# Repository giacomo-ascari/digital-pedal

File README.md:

# DIGITAL PEDAL - G33KY-TOAD
This project aims at the creation of a multi-effect stompbox.
```
        ┌─┐_┌───┐    ┌─────┐    ┌───────┐    ┌─────┐       /│   \
┌┴┴┐════┴═════  │    │ ADC │    │  MCU  │    │ DAC │    ┌─┤ │  \ \
└┬┬┘════┬═════  │ -> │     │ -> │ [DSP] │ -> │     │ -> └─┤ │  / /
        └─┘‾└───┘    └─────┘    └───────┘    └─────┘       \│   /
                     └─────────────────────────────┘
                                G33KY-TOAD
                             [DIGITAL-PEDAL]
```

## Hardware
The system will have a STM32F407VGT6 at it's core, with its 168Mhz clock and 192kB of memory.
ADC? Still don't know.
DAC? Probably one already on the STM32F4 MCU.

## Pedals
|           Name          |     Family     |             DSP             | Amplitude | Time/ frequency | Implemented |
|:-----------------------:|:--------------:|:---------------------------:|:---------:|:---------------:|:-----------:|
| Amplifier               | Utilities      | Gain > hard clip            |     X     |                 |      X      |
| Bypass                  | Utilities      | Bypass signal (default)     |           |                 |      X      |
| Bitcrusher (resolution) | Distortion     | Reduce sample resolution    |     X     |                 |      X      |
| Dynamic amplifier       | Utilities      | Gain > hard clip            |     X     |        X        |     WIP     |
| Fuzz                    | Distortion     | Gain > hard clip > sum wave |     X     |                 |      X      |
| Low pass filter         | Filter         | Low pass filter             |           |        X        |      X      |
| Overdrive               | Distortion     | Gain > soft clip            |     X     |                 |      X      |
| Overdrive (log)         | Distortion     | Gain > soft clip            |     X     |                 |      X      |
| Tremolo                 | Distortion     | Multiply by wave            |     X     |                 |      X      |

## Would-be-nice-to-have pedals
|           Name          |     Family     |             DSP             | Amplitude | Time/ frequency |
|:-----------------------:|:--------------:|:---------------------------:|:---------:|:---------------:|
| Bitcrusher (rate)       | Distortion     | Reduce sampling rate        |           |        X        |
| Wah wah                 | Filter         |                             |           |        X        |
| Compressor              | Compression    |                             |     X     |        X        |
| Equalizer               | Equalisation   |                             |     X     |        X        |
| Delay/echo              | Delay Lines    |                             |           |        X        |
| Vibrato                 | Distortion     |                             |           |        X        |
| Flanger                 | Flangers       |                             |           |                 |
| Phaser                  | Phasers        |                             |           |        X        |
| Octaver                 | Pitch Shifting |                             |           |        X        |
| Chorus                  | Chorus         |                             |           |        X        |

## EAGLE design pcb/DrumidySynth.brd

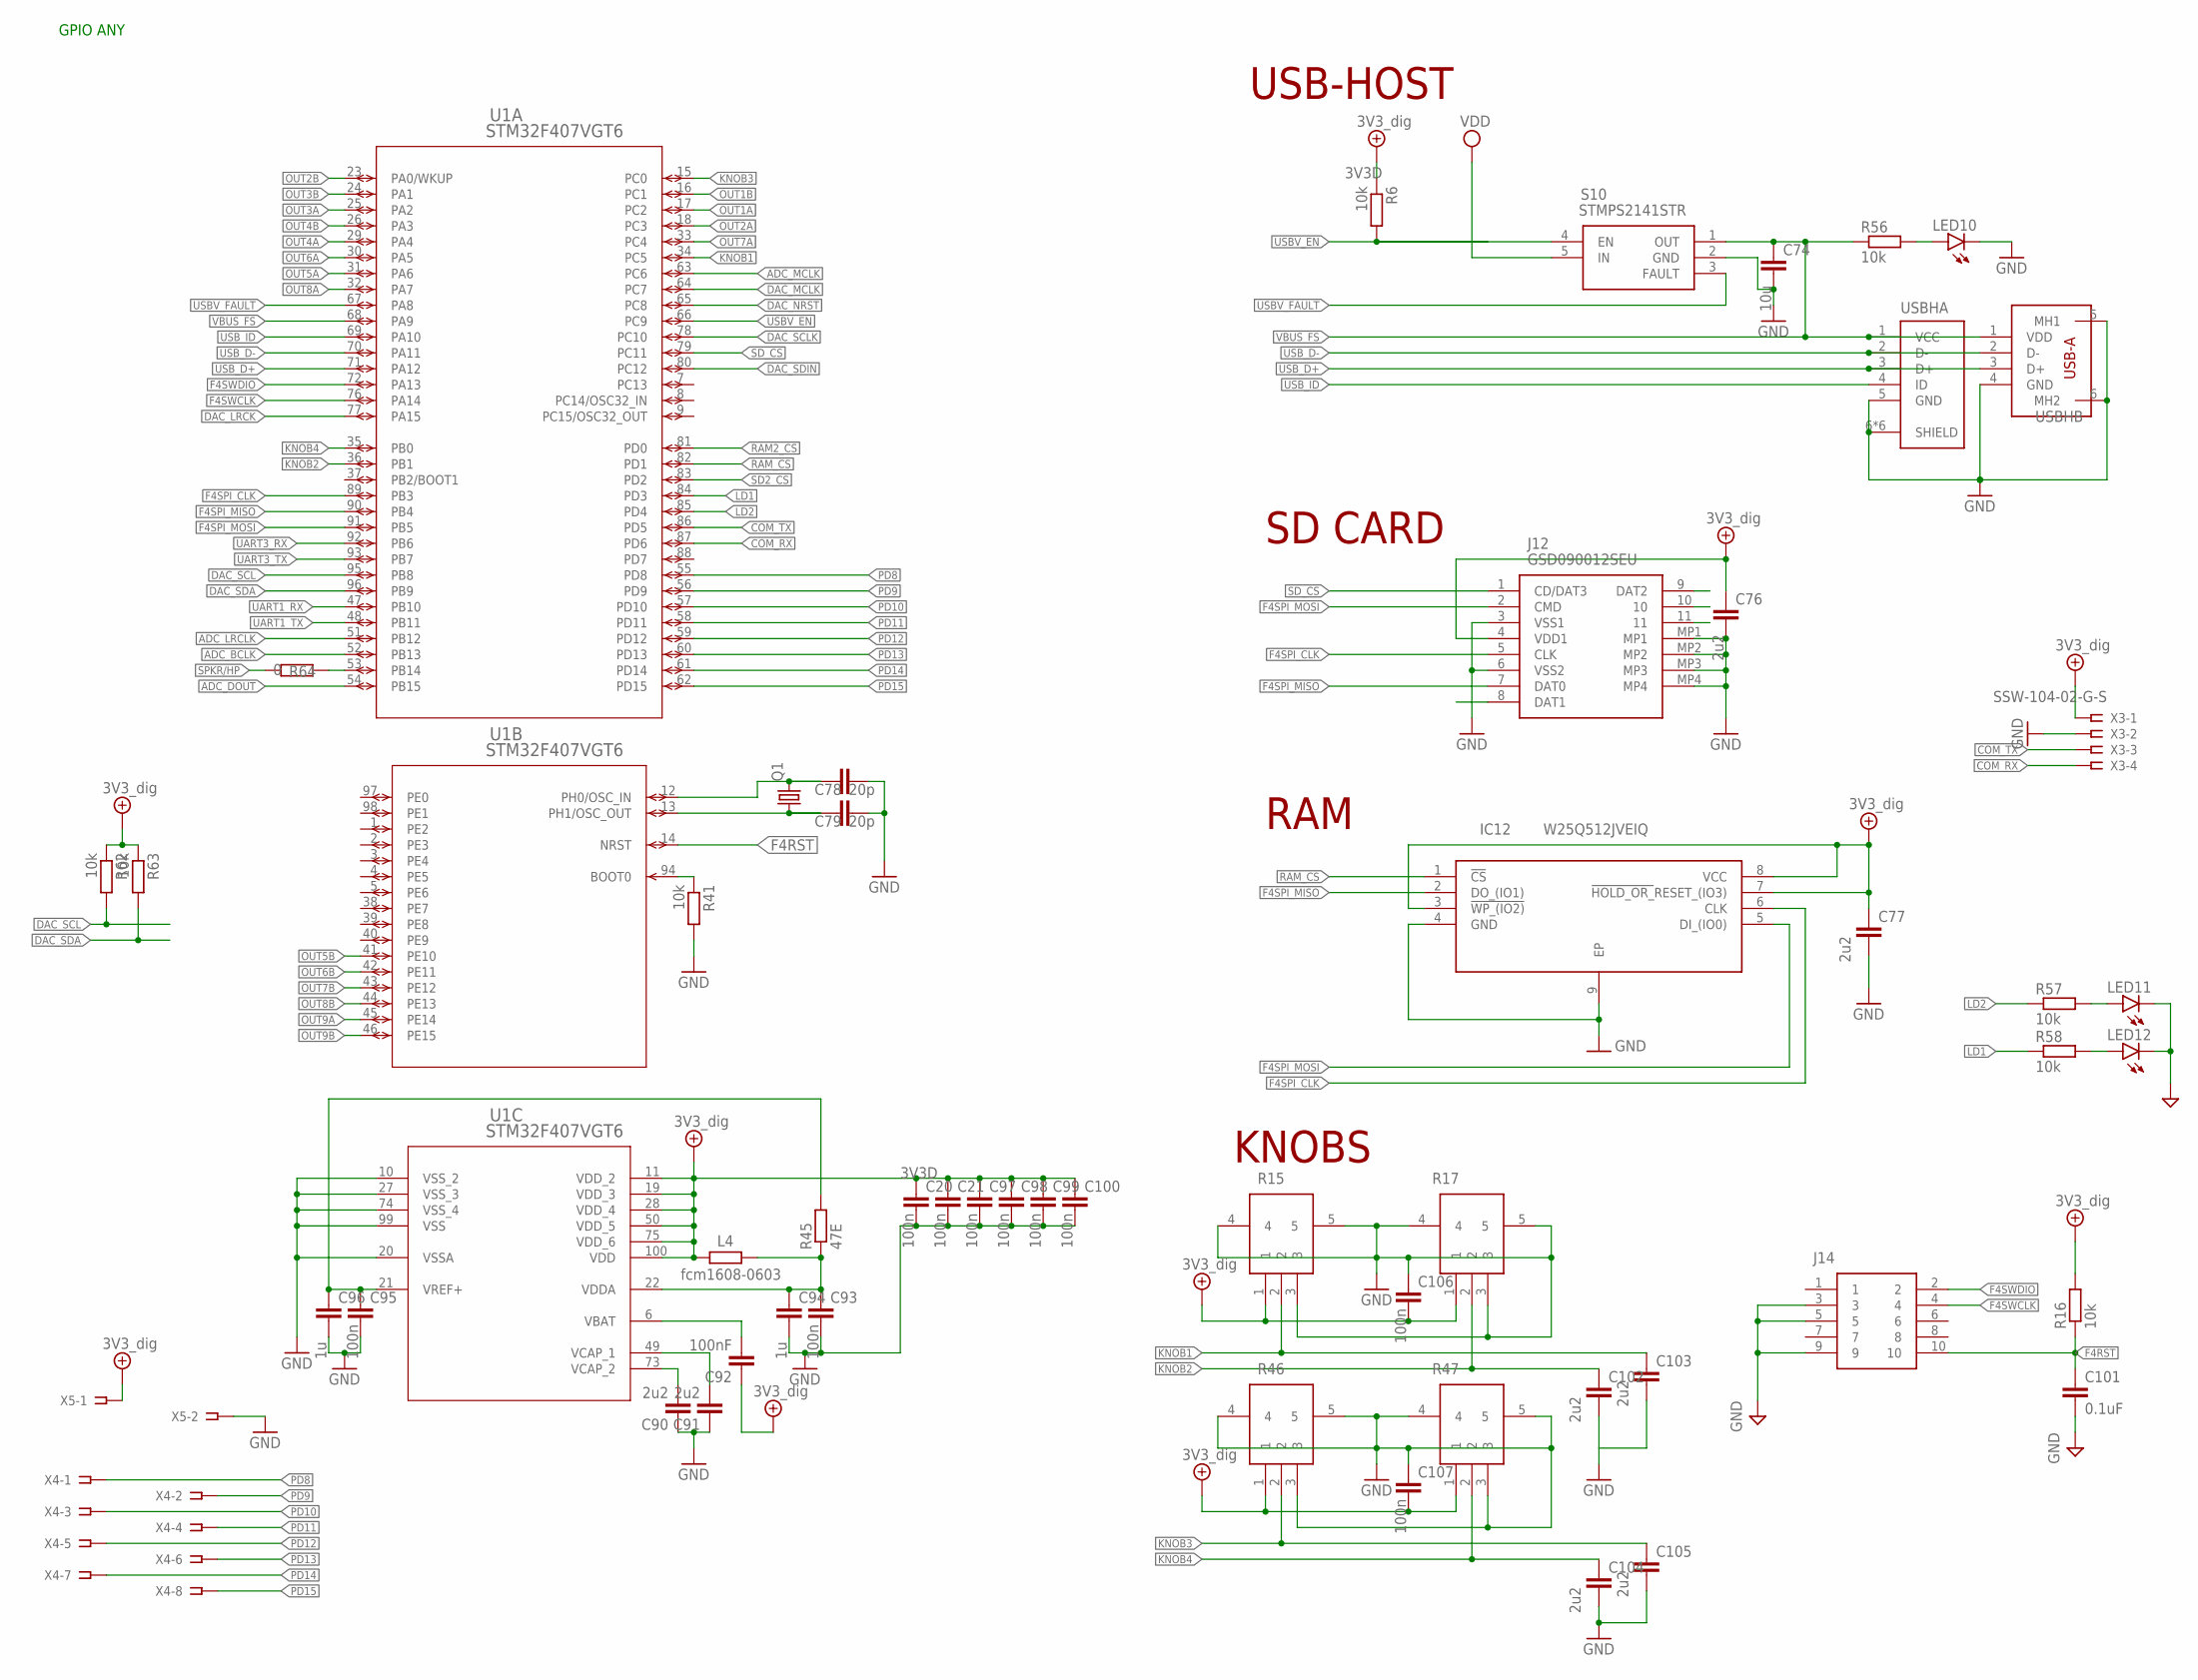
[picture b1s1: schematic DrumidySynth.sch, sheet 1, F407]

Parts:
C20, C21, C93, C95, C97, C98, C99, C100, C106, C107: 100n; C0603K
C74: 10u; C0805K
C76, C77, C102, C103, C104, C105: 2u2; C0805K
C78, C79: 20p; C0402K
C90, C91: 2u2; C0603K
C92: 100nF; C0603K
C94, C96: 1u; C0805K
C101: 0.1uF; C0402
IC12: W25Q512JVEIQ; SON127P800X600X80-9N
J12: GSD090012SEU
J14: FTSH-105-01-F-DV-K-A-P-TR; FTSH-105-XX-YYY-DV-K-A-P-TR
L4: fcm1608-0603; R0603
LED10, LED11, LED12: LEDCHIP-LED0603; CHIP-LED0603
Q1: CRYSTALHC49S; HC49/S
R6, R16, R41, R56, R57, R58, R62, R63: 10k; R0603
R15, R17, R46, R47: PTV09A-4025U-B103; PTV09A4020FB103
R45: 47E; R0603
R64: 0; R0603
S10: STMPS2141STR; SOT95P280X145-5N
U1: STM32F407VGT6; LQFP100-14X14MM
USBHA: 10103594-0001LF; AMPHENOL_10103594-0001LF
USBHB: USB-A(292303-7); 2923037
X3: SSW-104-02-G-S
X4: SSW-104-02-G-D
X5: SSW-102-02-G-S

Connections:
3V3D: C20.1, C21.1, C76.1, C77.1, C92.1, C97.1, C98.1, C99.1, C100.1, C106.2, C107.2, IC12.3 (!WP_(IO2)), IC12.7 (!HOLD_OR_!RESET_(IO3)), IC12.8 (VCC), J12.4 (VDD1), L4.2, R6.1, R15.1, R16.2, R17.1, R46.1, R47.1, R62.1, R63.1, U1.11 (VDD_2), U1.19 (VDD_3), U1.28 (VDD_4), U1.50 (VDD_5), U1.75 (VDD_6), U1.100 (VDD), X3.1, X5.1; also elsewhere on the board
ADC_BCLK: U1.52 (PB13); also elsewhere on the board
ADC_DOUT: U1.54 (PB15); also elsewhere on the board
ADC_LRCLK: U1.51 (PB12); also elsewhere on the board
ADC_MCLK: U1.63 (PC6); also elsewhere on the board
COM_RX: U1.87 (PD6), X3.4
COM_TX: U1.86 (PD5), X3.3
DAC_LRCK: U1.77 (PA15); also elsewhere on the board
DAC_MCLK: U1.64 (PC7); also elsewhere on the board
DAC_NRST: U1.65 (PC8); also elsewhere on the board
DAC_SCL: R62.2, U1.95 (PB8); also elsewhere on the board
DAC_SCLK: U1.78 (PC10); also elsewhere on the board
DAC_SDA: R63.2, U1.96 (PB9); also elsewhere on the board
DAC_SDIN: U1.80 (PC12); also elsewhere on the board
F4RST: C101.1, J14.10, R16.1, U1.14 (NRST)
F4SPI_CLK: IC12.6 (CLK), J12.5 (CLK), U1.89 (PB3); also elsewhere on the board
F4SPI_MISO: IC12.2 (DO_(IO1)), J12.7 (DAT0), U1.90 (PB4); also elsewhere on the board
F4SPI_MOSI: IC12.5 (DI_(IO0)), J12.2 (CMD), U1.91 (PB5); also elsewhere on the board
F4SWCLK: J14.4, U1.76 (PA14)
F4SWDIO: J14.2, U1.72 (PA13)
GND: C20.2, C21.2, C74.2, C76.2, C77.2, C78.2, C79.2, C90.1, C91.1, C93.2, C94.2, C95.2, C96.2, C97.2, C98.2, C99.2, C100.2, C101.2, C102.2, C103.2, C104.2, C105.2, C106.1, C107.1, IC12.4 (GND), IC12.9 (EP), J12.3 (VSS1), J12.6 (VSS2), J12.MP1, J12.MP2, J12.MP3, J12.MP4, J14.3, J14.5, J14.9, LED10.C, LED11.C, LED12.C, R15.3, R15.4, R15.5, R17.3, R17.4, R17.5, R41.2, R46.3, R46.4, R46.5, R47.3, R47.4, R47.5, S10.2 (GND), U1.10 (VSS_2), U1.20 (VSSA), U1.27 (VSS_3), U1.74 (VSS_4), U1.99 (VSS), USBHA.5 (GND), USBHA.6 (SHIELD), USBHA.7 (SHIELD), USBHA.8 (SHIELD), USBHA.9 (SHIELD), USBHA.S1 (SHIELD), USBHA.S2 (SHIELD), USBHB.4 (GND), USBHB.5 (MH1), USBHB.6 (MH2), X3.2, X5.2; also elsewhere on the board
KNOB1: C103.1, R15.2, U1.34 (PC5)
KNOB2: C102.1, R17.2, U1.36 (PB1)
KNOB3: C105.1, R46.2, U1.15 (PC0)
KNOB4: C104.1, R47.2, U1.35 (PB0)
LD1: R58.1, U1.84 (PD3)
LD2: R57.1, U1.85 (PD4)
unnamed: R64.2, U1.53 (PB14)
unnamed: C78.1, Q1.2, U1.12 (PH0/OSC_IN)
unnamed: C79.1, Q1.1, U1.13 (PH1/OSC_OUT)
unnamed: R41.1, U1.94 (BOOT0)
unnamed: LED10.A, R56.2
unnamed: LED11.A, R57.2
unnamed: LED12.A, R58.2
unnamed: C90.2, U1.73 (VCAP_2)
unnamed: C91.2, U1.49 (VCAP_1)
unnamed: C92.2, U1.6 (VBAT)
unnamed: C93.1, C94.1, L4.1, R45.1, U1.22 (VDDA)
unnamed: C95.1, C96.1, R45.2, U1.21 (VREF+)
OUT1A: U1.17 (PC2); also elsewhere on the board
OUT1B: U1.16 (PC1); also elsewhere on the board
OUT2A: U1.18 (PC3); also elsewhere on the board
OUT2B: U1.23 (PA0/WKUP); also elsewhere on the board
OUT3A: U1.25 (PA2); also elsewhere on the board
OUT3B: U1.24 (PA1); also elsewhere on the board
OUT4A: U1.29 (PA4); also elsewhere on the board
OUT4B: U1.26 (PA3); also elsewhere on the board
OUT5A: U1.31 (PA6); also elsewhere on the board
OUT5B: U1.41 (PE10); also elsewhere on the board
OUT6A: U1.30 (PA5); also elsewhere on the board
OUT6B: U1.42 (PE11); also elsewhere on the board
OUT7A: U1.33 (PC4); also elsewhere on the board
OUT7B: U1.43 (PE12); also elsewhere on the board
OUT8A: U1.32 (PA7); also elsewhere on the board
OUT8B: U1.44 (PE13); also elsewhere on the board
OUT9A: U1.45 (PE14); also elsewhere on the board
OUT9B: U1.46 (PE15); also elsewhere on the board
PD8: U1.55 (PD8), X4.1
PD9: U1.56 (PD9), X4.2
PD10: U1.57 (PD10), X4.3
PD11: U1.58 (PD11), X4.4
PD12: U1.59 (PD12), X4.5
PD13: U1.60 (PD13), X4.6
PD14: U1.61 (PD14), X4.7
PD15: U1.62 (PD15), X4.8
RAM2_CS: U1.81 (PD0); also elsewhere on the board
RAM_CS: IC12.1 (!CS), U1.82 (PD1)
SD2_CS: U1.83 (PD2); also elsewhere on the board
SD_CS: J12.1 (CD/DAT3), U1.79 (PC11)
SPKR/HP: R64.1; also elsewhere on the board
UART1_RX: U1.47 (PB10); also elsewhere on the board
UART1_TX: U1.48 (PB11); also elsewhere on the board
UART3_RX: U1.92 (PB6); also elsewhere on the board
UART3_TX: U1.93 (PB7); also elsewhere on the board
USBV_EN: R6.2, S10.4 (EN), U1.66 (PC9)
USBV_FAULT: S10.3 (FAULT), U1.67 (PA8)
USB_D+: U1.71 (PA12), USBHA.3 (D+), USBHB.3 (D+)
USB_D-: U1.70 (PA11), USBHA.2 (D-), USBHB.2 (D-)
USB_ID: U1.69 (PA10), USBHA.4 (ID)
VBUS_FS: C74.1, R56.1, S10.1 (OUT), U1.68 (PA9), USBHA.1 (VCC), USBHB.1 (VDD)
VIN: S10.5 (IN); also elsewhere on the board

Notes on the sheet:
RAM
USB-HOST
SD CARD
GPIO ANY
KNOBS

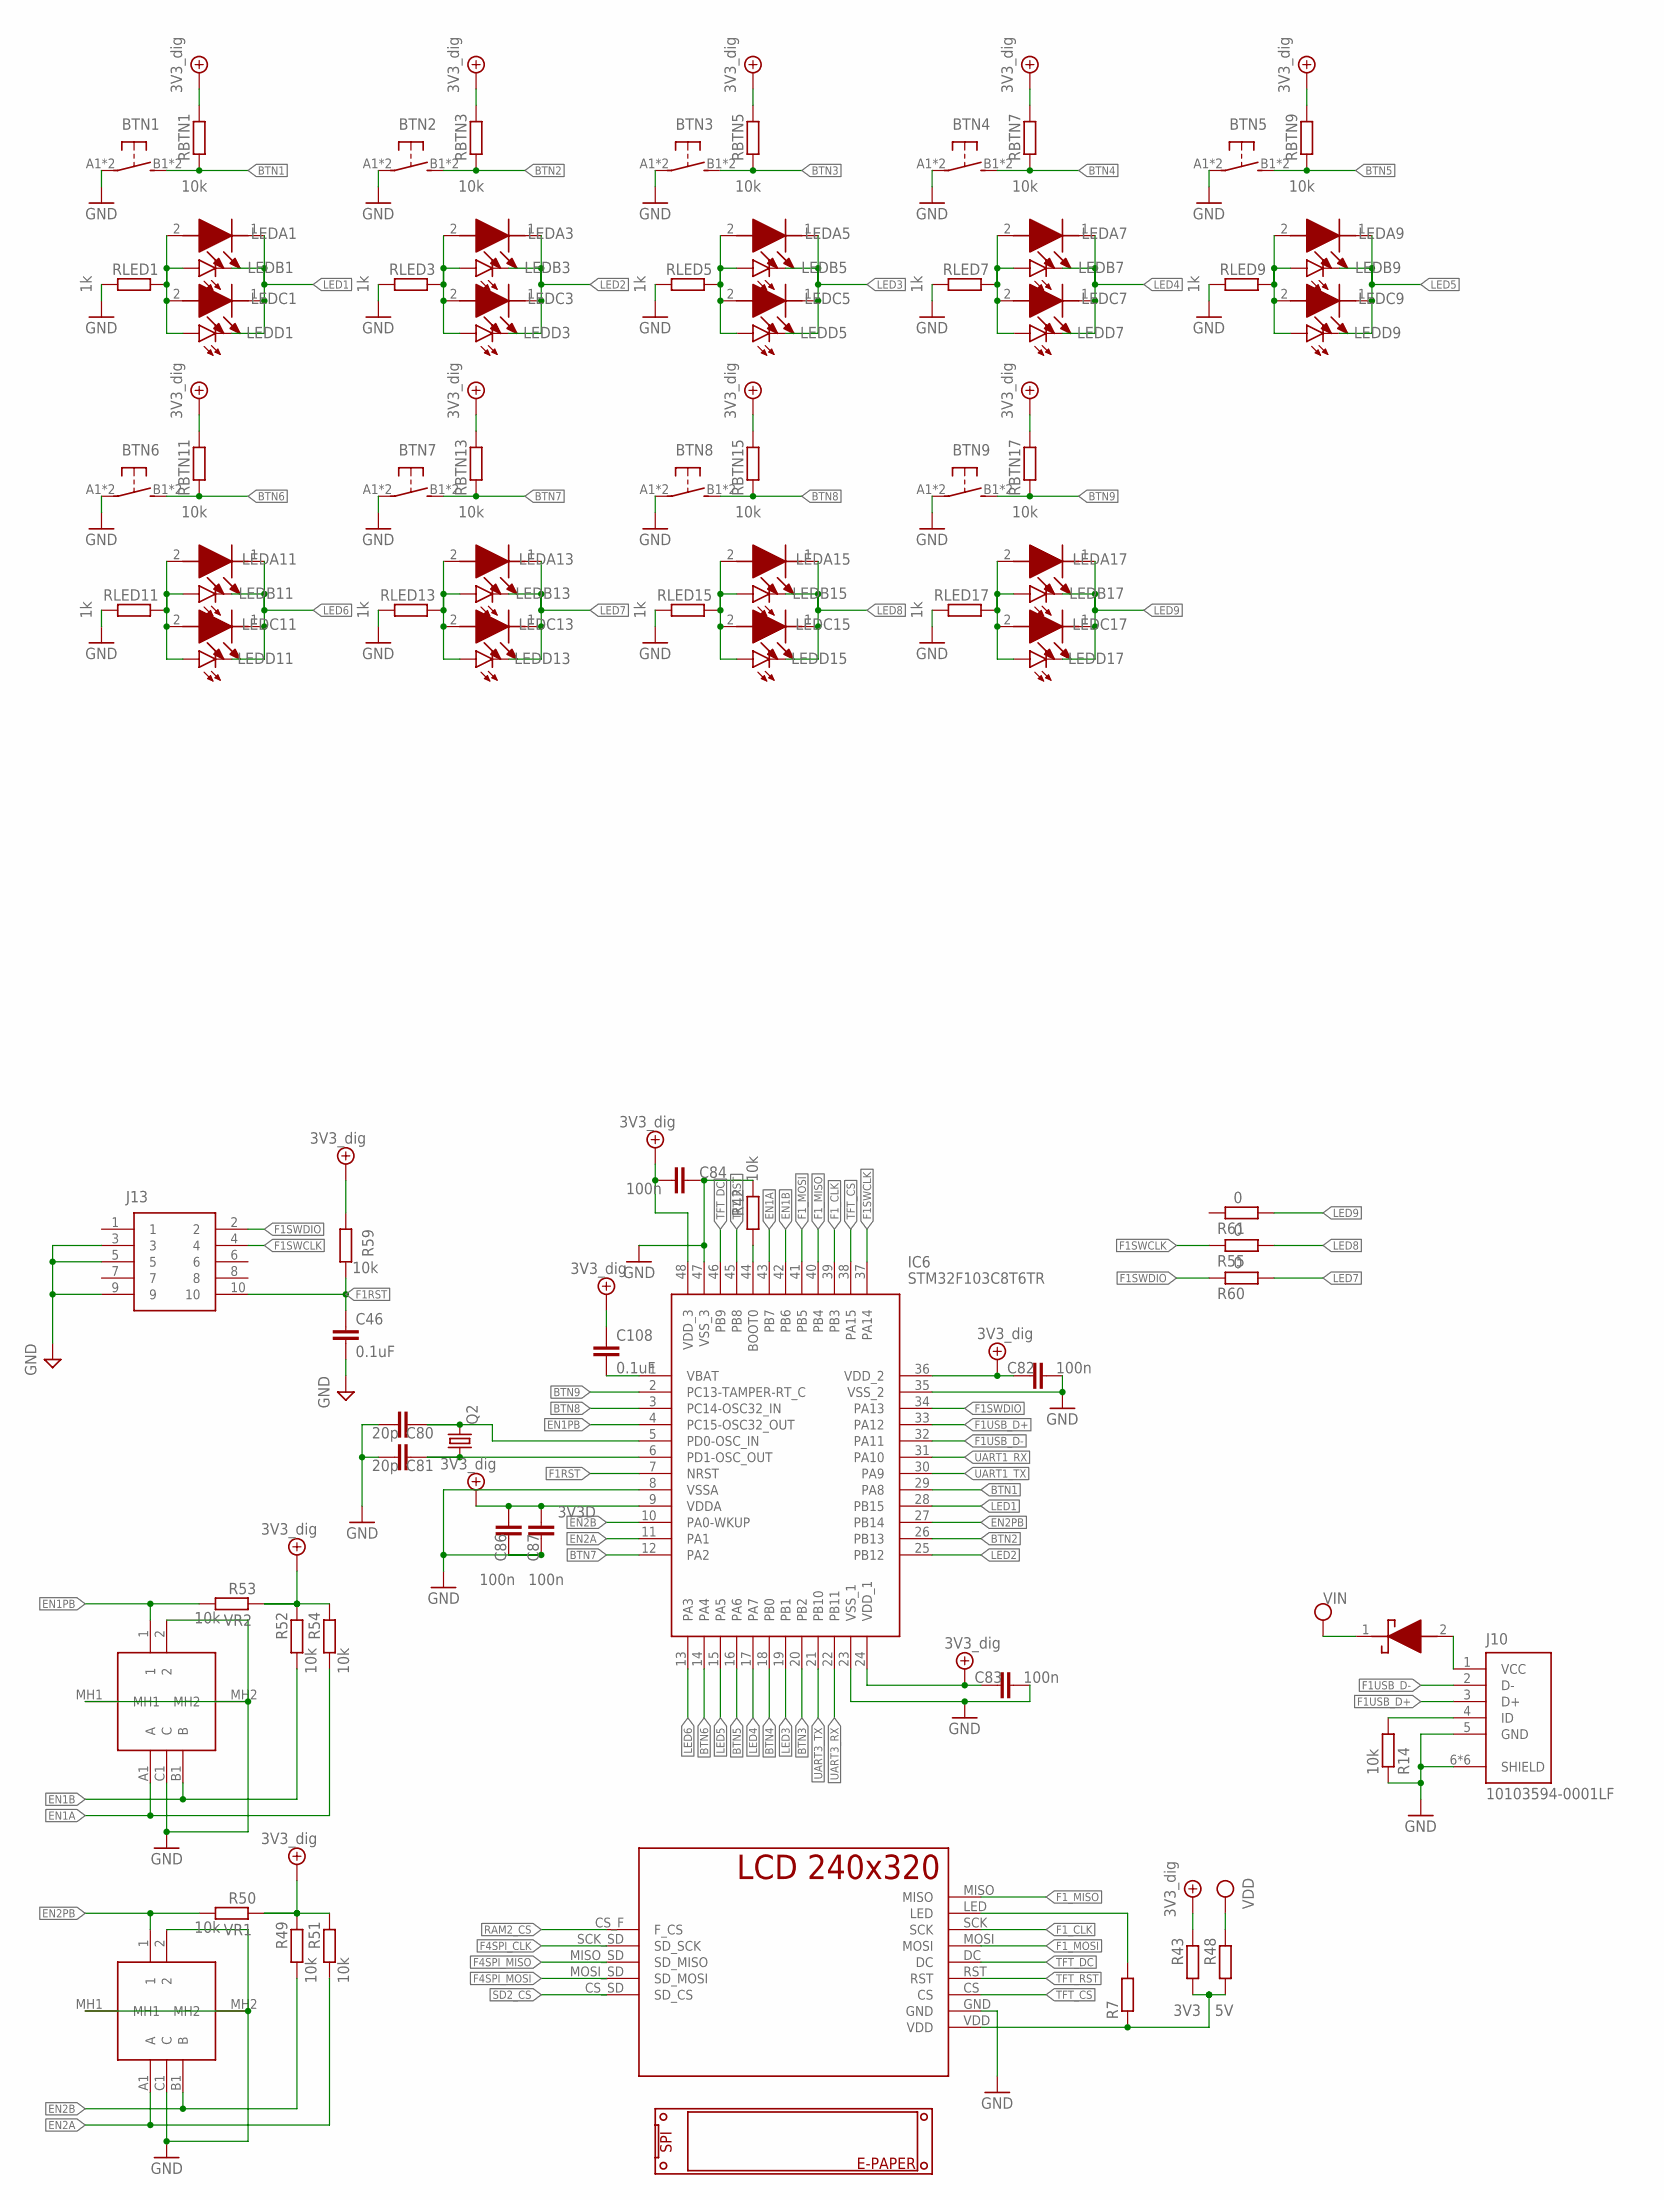
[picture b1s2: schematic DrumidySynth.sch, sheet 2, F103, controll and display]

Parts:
BTN1, BTN2, BTN3, BTN4, BTN5, BTN6, BTN7, BTN8, BTN9: 31-XX; B3F-31XX
C46, C108: 0.1uF; C0402
C80, C81: 20p; C0402K
C82, C83, C84, C86, C87: 100n; C0603K
D1R1: BAT54J,115; SODFL2512X80N
IC6: STM32F103C8T6TR; QFP50P900X900X160-48N
J10: 10103594-0001LF; AMPHENOL_10103594-0001LF
J13: FTSH-105-01-F-DV-K-A-P-TR; FTSH-105-XX-YYY-DV-K-A-P-TR
LEDA1, LEDA3, LEDA5, LEDA7, LEDA9, LEDA11, LEDA13, LEDA15, LEDA17: L-934HD; T-1(3MM)_2
LEDB1, LEDB3, LEDB5, LEDB7, LEDB9, LEDB11, LEDB13, LEDB15, LEDB17: LEDCHIP-LED0603; CHIP-LED0603
LEDC1, LEDC3, LEDC5, LEDC7, LEDC9, LEDC11, LEDC13, LEDC15, LEDC17: L-934HD; T-1(3MM)_2
LEDD1, LEDD3, LEDD5, LEDD7, LEDD9, LEDD11, LEDD13, LEDD15, LEDD17: LEDCHIP-LED0603; CHIP-LED0603
Q2: CRYSTALHC49S; HC49/S
R7: R-EU_R0805; R0805
R14, R42, R49, R50, R51, R52, R53, R54, R59: 10k; R0603
R43: 3V3; R0603
R48: 5V; R0603
R55, R60, R61: 0; R0603
RBTN1, RBTN3, RBTN5, RBTN7, RBTN9, RBTN11, RBTN13, RBTN15, RBTN17: 10k; R0603
RLED1, RLED3, RLED5, RLED7, RLED9, RLED11, RLED13, RLED15, RLED17: 1k; R0603
U$2: TFT-SD; TFTQVGA
U$3: EPAPER2.9; EPAPERLCDNOPIN
VR1, VR2: PEC11R-4220F-S0024; PEC11R4220FS0024

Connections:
3V3D: C82.1, C83.1, C84.2, C86.2, C87.2, C108.1, IC6.9 (VDDA), IC6.24 (VDD_1), IC6.36 (VDD_2), IC6.48 (VDD_3), R43.1, R49.1, R50.1, R51.1, R52.1, R53.1, R54.1, R59.2, RBTN1.1, RBTN3.1, RBTN5.1, RBTN7.1, RBTN9.1, RBTN11.1, RBTN13.1, RBTN15.1, RBTN17.1; also elsewhere on the board
BTN1: BTN1.B1 (S), BTN1.B2 (S), IC6.29 (PA8), RBTN1.2
BTN2: BTN2.B1 (S), BTN2.B2 (S), IC6.26 (PB13), RBTN3.2
BTN3: BTN3.B1 (S), BTN3.B2 (S), IC6.20 (PB2), RBTN5.2
BTN4: BTN4.B1 (S), BTN4.B2 (S), IC6.18 (PB0), RBTN7.2
BTN5: BTN5.B1 (S), BTN5.B2 (S), IC6.16 (PA6), RBTN9.2
BTN6: BTN6.B1 (S), BTN6.B2 (S), IC6.14 (PA4), RBTN11.2
BTN7: BTN7.B1 (S), BTN7.B2 (S), IC6.12 (PA2), RBTN13.2
BTN8: BTN8.B1 (S), BTN8.B2 (S), IC6.3 (PC14-OSC32_IN), RBTN15.2
BTN9: BTN9.B1 (S), BTN9.B2 (S), IC6.2 (PC13-TAMPER-RT_C), RBTN17.2
EN1A: IC6.43 (PB7), R54.2, VR2.A1 (A)
EN1B: IC6.42 (PB6), R52.2, VR2.B1 (B)
EN1PB: IC6.4 (PC15-OSC32_OUT), R53.2, VR2.1
EN2A: IC6.11 (PA1), R51.2, VR1.A1 (A)
EN2B: IC6.10 (PA0-WKUP), R49.2, VR1.B1 (B)
EN2PB: IC6.27 (PB14), R50.2, VR1.1
F1RST: C46.1, IC6.7 (NRST), J13.10, R59.1
F1SWCLK: IC6.37 (PA14), J13.4, R55.1
F1SWDIO: IC6.34 (PA13), J13.2, R60.1
F1USB_D+: IC6.33 (PA12), J10.3 (D+)
F1USB_D-: IC6.32 (PA11), J10.2 (D-)
F1_CLK: IC6.39 (PB3), U$2.SCK
F1_MISO: IC6.40 (PB4), U$2.MISO
F1_MOSI: IC6.41 (PB5), U$2.MOSI
F4SPI_CLK: U$2.SCK_SD (SD_SCK); also elsewhere on the board
F4SPI_MISO: U$2.MISO_SD (SD_MISO); also elsewhere on the board
F4SPI_MOSI: U$2.MOSI_SD (SD_MOSI); also elsewhere on the board
GND: BTN1.A1, BTN1.A2, BTN2.A1, BTN2.A2, BTN3.A1, BTN3.A2, BTN4.A1, BTN4.A2, BTN5.A1, BTN5.A2, BTN6.A1, BTN6.A2, BTN7.A1, BTN7.A2, BTN8.A1, BTN8.A2, BTN9.A1, BTN9.A2, C46.2, C80.2, C81.2, C82.2, C83.2, C84.1, C86.1, C87.1, IC6.8 (VSSA), IC6.23 (VSS_1), IC6.35 (VSS_2), IC6.47 (VSS_3), J10.5 (GND), J10.6 (SHIELD), J10.7 (SHIELD), J10.8 (SHIELD), J10.9 (SHIELD), J10.S1 (SHIELD), J10.S2 (SHIELD), J13.3, J13.5, J13.9, R14.1, R42.1, RLED1.2, RLED3.2, RLED5.2, RLED7.2, RLED9.2, RLED11.2, RLED13.2, RLED15.2, RLED17.2, U$2.GND, VR1.2, VR1.C1 (C), VR1.MH1, VR1.MH2, VR2.2, VR2.C1 (C), VR2.MH1, VR2.MH2; also elsewhere on the board
LED1: IC6.28 (PB15), LEDA1.1 (K), LEDB1.C, LEDC1.1 (K), LEDD1.C
LED2: IC6.25 (PB12), LEDA3.1 (K), LEDB3.C, LEDC3.1 (K), LEDD3.C
LED3: IC6.19 (PB1), LEDA5.1 (K), LEDB5.C, LEDC5.1 (K), LEDD5.C
LED4: IC6.17 (PA7), LEDA7.1 (K), LEDB7.C, LEDC7.1 (K), LEDD7.C
LED5: IC6.15 (PA5), LEDA9.1 (K), LEDB9.C, LEDC9.1 (K), LEDD9.C
LED6: IC6.13 (PA3), LEDA11.1 (K), LEDB11.C, LEDC11.1 (K), LEDD11.C
LED7: LEDA13.1 (K), LEDB13.C, LEDC13.1 (K), LEDD13.C, R60.2
LED8: LEDA15.1 (K), LEDB15.C, LEDC15.1 (K), LEDD15.C, R55.2
LED9: LEDA17.1 (K), LEDB17.C, LEDC17.1 (K), LEDD17.C, R61.2
unnamed: C80.1, IC6.5 (PD0-OSC_IN), Q2.2
unnamed: C81.1, IC6.6 (PD1-OSC_OUT), Q2.1
unnamed: IC6.44 (BOOT0), R42.2
unnamed: C108.2, IC6.1 (VBAT)
unnamed: D1R1.2 (A), J10.1 (VCC)
unnamed: J10.4 (ID), R14.2
unnamed: R7.2, U$2.LED
unnamed: R7.1, R43.2, R48.2, U$2.VDD
unnamed: LEDA1.2 (A), LEDB1.A, LEDC1.2 (A), LEDD1.A, RLED1.1
unnamed: LEDA3.2 (A), LEDB3.A, LEDC3.2 (A), LEDD3.A, RLED3.1
unnamed: LEDA5.2 (A), LEDB5.A, LEDC5.2 (A), LEDD5.A, RLED5.1
unnamed: LEDA7.2 (A), LEDB7.A, LEDC7.2 (A), LEDD7.A, RLED7.1
unnamed: LEDA9.2 (A), LEDB9.A, LEDC9.2 (A), LEDD9.A, RLED9.1
unnamed: LEDA11.2 (A), LEDB11.A, LEDC11.2 (A), LEDD11.A, RLED11.1
unnamed: LEDA13.2 (A), LEDB13.A, LEDC13.2 (A), LEDD13.A, RLED13.1
unnamed: LEDA15.2 (A), LEDB15.A, LEDC15.2 (A), LEDD15.A, RLED15.1
unnamed: LEDA17.2 (A), LEDB17.A, LEDC17.2 (A), LEDD17.A, RLED17.1
RAM2_CS: U$2.CS_F (F_CS); also elsewhere on the board
SD2_CS: U$2.CS_SD (SD_CS); also elsewhere on the board
TFT_CS: IC6.38 (PA15), U$2.CS
TFT_DC: IC6.46 (PB9), U$2.DC
TFT_RST: IC6.45 (PB8), U$2.RST
UART1_RX: IC6.31 (PA10); also elsewhere on the board
UART1_TX: IC6.30 (PA9); also elsewhere on the board
UART3_RX: IC6.22 (PB11); also elsewhere on the board
UART3_TX: IC6.21 (PB10); also elsewhere on the board
VIN: D1R1.1 (K), R48.1; also elsewhere on the board

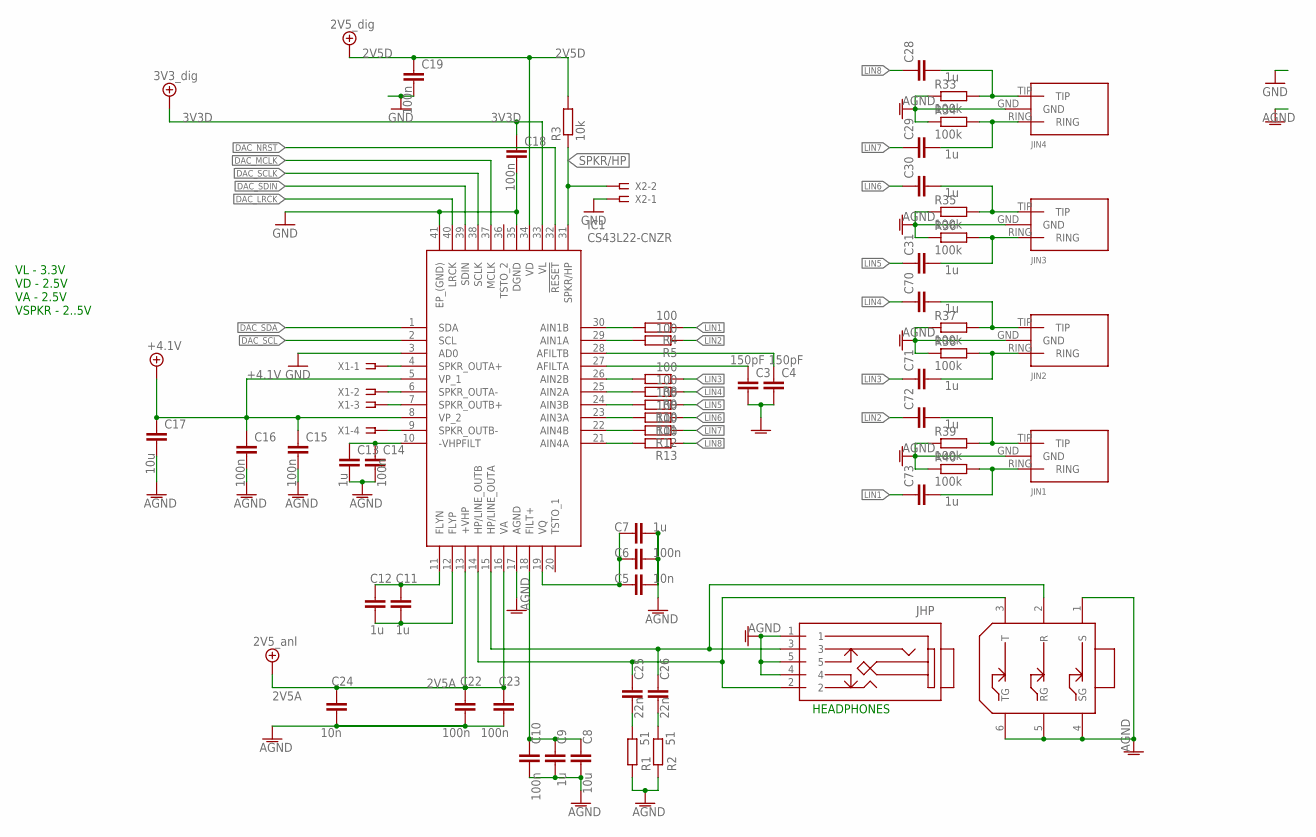
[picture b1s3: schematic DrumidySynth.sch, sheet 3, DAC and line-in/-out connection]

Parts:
C3, C4: 150pF; C0402K
C5, C24: 10n; C0402K
C6, C10, C14, C15, C16, C18, C19, C22, C23: 100n; C0603K
C7, C9, C11, C12, C13, C28, C29, C30, C31, C70, C71, C72, C73: 1u; C0603K
C8, C17: 10u; C0805K
C25, C26: 22n; C0603K
IC1: CS43L22-CNZR; QFN50P600X600X100-41N
JHP: 35RAPC2AVN4
JIN1, JIN2, JIN3, JIN4: JACK35VERT
JOUT: SJ-63073E; SJ63073E
R1, R2: 51; R0603
R3: 10k; R0603
R4, R5, R8, R9, R10, R11, R12, R13: 100; R0603
R33, R34, R35, R36, R37, R38, R39, R40: 100k; R0603
X1: SSW-104-02-G-S
X2: SSW-102-02-G-S

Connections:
2V5A: C22.1, C23.1, C24.1, IC1.13 (+VHP), IC1.16 (VA); also elsewhere on the board
2V5D: C19.1, IC1.34 (VD), R3.2; also elsewhere on the board
3V3D: C18.1, IC1.33 (VL); also elsewhere on the board
+4.1V: C15.1, C16.1, C17.1, IC1.5 (VP_1), IC1.8 (VP_2); also elsewhere on the board
DAC_LRCK: IC1.40 (LRCK); also elsewhere on the board
DAC_MCLK: IC1.37 (MCLK); also elsewhere on the board
DAC_NRST: IC1.32 (!RESET); also elsewhere on the board
DAC_SCL: IC1.2 (SCL); also elsewhere on the board
DAC_SCLK: IC1.38 (SCLK); also elsewhere on the board
DAC_SDA: IC1.1 (SDA); also elsewhere on the board
DAC_SDIN: IC1.39 (SDIN); also elsewhere on the board
GND: C3.2, C4.2, C5.2, C6.2, C7.2, C8.2, C9.2, C10.2, C13.2, C14.2, C15.2, C16.2, C17.2, C18.2, C19.2, C22.2, C23.2, C24.2, IC1.3 (AD0), IC1.17 (AGND), IC1.35 (DGND), IC1.41 (EP_(GND)), JHP.1, JHP.4, JHP.5, JIN1.GND, JIN2.GND, JIN3.GND, JIN4.GND, JOUT.1 (S), JOUT.4 (SG), JOUT.5 (RG), JOUT.6 (TG), R1.1, R2.1, R33.1, R34.1, R35.1, R36.1, R37.1, R38.1, R39.1, R40.1, X2.1; also elsewhere on the board
LIN1: C73.1, R4.1
LIN2: C72.1, R5.1
LIN3: C71.1, R8.1
LIN4: C70.1, R9.1
LIN5: C31.1, R10.1
LIN6: C30.1, R11.1
LIN7: C29.1, R12.1
LIN8: C28.1, R13.1
unnamed: C3.1, IC1.27 (AFILTA)
unnamed: C4.1, IC1.28 (AFILTB)
unnamed: C5.1, C6.1, C7.1, IC1.19 (VQ)
unnamed: C8.1, C9.1, C10.1, IC1.18 (FILT+)
unnamed: C11.1, C12.1, IC1.11 (FLYN)
unnamed: C11.2, C12.2, IC1.12 (FLYP)
unnamed: C13.1, C14.1, IC1.10 (-VHPFILT)
unnamed: IC1.9 (SPKR_OUTB-), X1.4
unnamed: IC1.7 (SPKR_OUTB+), X1.3
unnamed: IC1.6 (SPKR_OUTA-), X1.2
unnamed: IC1.4 (SPKR_OUTA+), X1.1
unnamed: C25.1, IC1.14 (HP/LINE_OUTB), JHP.2, JOUT.3 (T)
unnamed: C26.1, IC1.15 (HP/LINE_OUTA), JHP.3, JOUT.2 (R)
unnamed: C25.2, R1.2
unnamed: C26.2, R2.2
unnamed: IC1.30 (AIN1B), R4.2
unnamed: IC1.29 (AIN1A), R5.2
unnamed: IC1.26 (AIN2B), R8.2
unnamed: IC1.25 (AIN2A), R9.2
unnamed: IC1.24 (AIN3B), R10.2
unnamed: IC1.23 (AIN3A), R11.2
unnamed: IC1.22 (AIN4B), R12.2
unnamed: IC1.21 (AIN4A), R13.2
unnamed: C73.2, JIN1.RING, R40.2
unnamed: C72.2, JIN1.TIP, R39.2
unnamed: C71.2, JIN2.RING, R38.2
unnamed: C70.2, JIN2.TIP, R37.2
unnamed: C31.2, JIN3.RING, R36.2
unnamed: C30.2, JIN3.TIP, R35.2
unnamed: C29.2, JIN4.RING, R34.2
unnamed: C28.2, JIN4.TIP, R33.2
SPKR/HP: IC1.31 (SPKR/HP), R3.1, X2.2; also elsewhere on the board

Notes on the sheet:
HEADPHONES
VL - 3.3V VD - 2.5V VA - 2.5V VSPKR - 2..5V

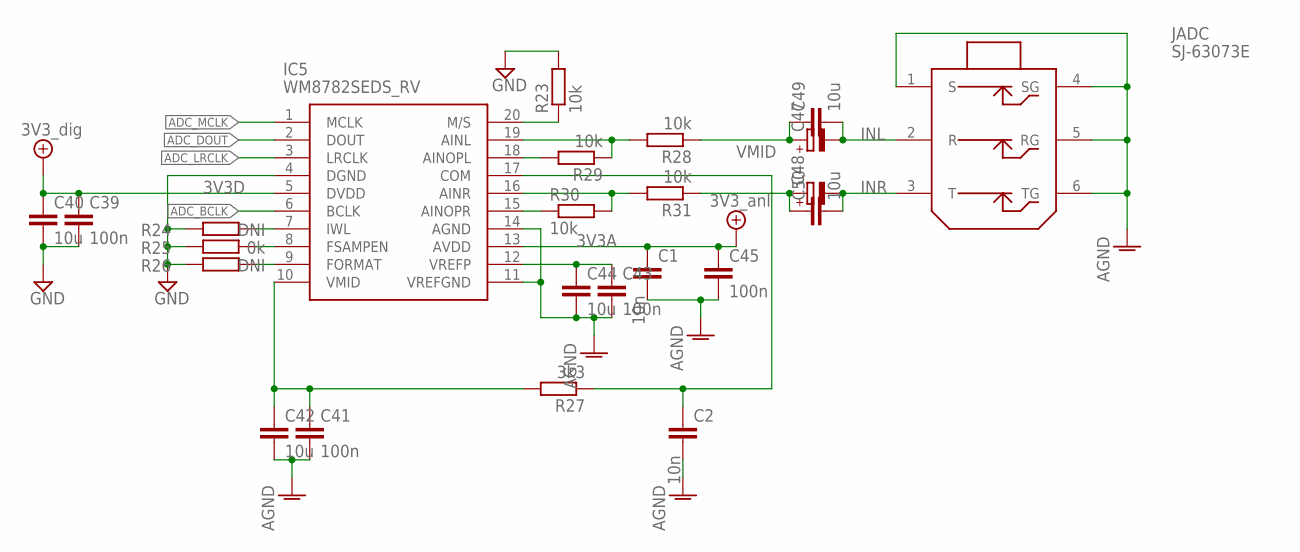
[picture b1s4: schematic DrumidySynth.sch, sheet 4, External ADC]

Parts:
C1, C2: 10n; C0402K
C39, C41, C43, C45: 100n; C0603K
C40, C42, C44: 10u; C0603K
C47, C48: CPOL-EUE2-5; E2-5
C49, C50: 10u; C0805
IC5: WM8782SEDS_RV; SOP65P780X200-20N
JADC: SJ-63073E; SJ63073E
R23, R28, R29, R30, R31: 10k; R0603
R24, R26: DNI; R0603
R25: 0k; R0603
R27: 3k3; R0603

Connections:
3V3A: C1.1, C45.1, IC5.13 (AVDD); also elsewhere on the board
3V3D: C39.1, C40.1, IC5.5 (DVDD); also elsewhere on the board
ADC_BCLK: IC5.6 (BCLK); also elsewhere on the board
ADC_DOUT: IC5.2 (DOUT); also elsewhere on the board
ADC_LRCLK: IC5.3 (LRCLK); also elsewhere on the board
ADC_MCLK: IC5.1 (MCLK); also elsewhere on the board
GND: C1.2, C2.2, C39.2, C40.2, C41.2, C42.2, C43.2, C44.2, C45.2, IC5.4 (DGND), IC5.11 (VREFGND), IC5.14 (AGND), JADC.1 (S), JADC.4 (SG), JADC.5 (RG), JADC.6 (TG), R23.2, R24.1, R25.1, R26.1; also elsewhere on the board
INL: C47.-, C49.2, JADC.2 (R)
INR: C48.-, C50.2, JADC.3 (T)
unnamed: IC5.20 (M/S), R23.1
unnamed: IC5.7 (IWL), R24.2
unnamed: IC5.8 (FSAMPEN), R25.2
unnamed: IC5.9 (FORMAT), R26.2
unnamed: C43.1, C44.1, IC5.12 (VREFP)
unnamed: C2.1, IC5.17 (COM), R27.1
unnamed: IC5.18 (AINOPL), R29.2
unnamed: IC5.16 (AINR), R30.2, R31.2
unnamed: IC5.15 (AINOPR), R30.1
unnamed: IC5.19 (AINL), R28.2, R29.1
unnamed: C47.+, C49.1, R28.1
unnamed: C48.+, C50.1, R31.1
VMID: C41.1, C42.1, IC5.10 (VMID), R27.2

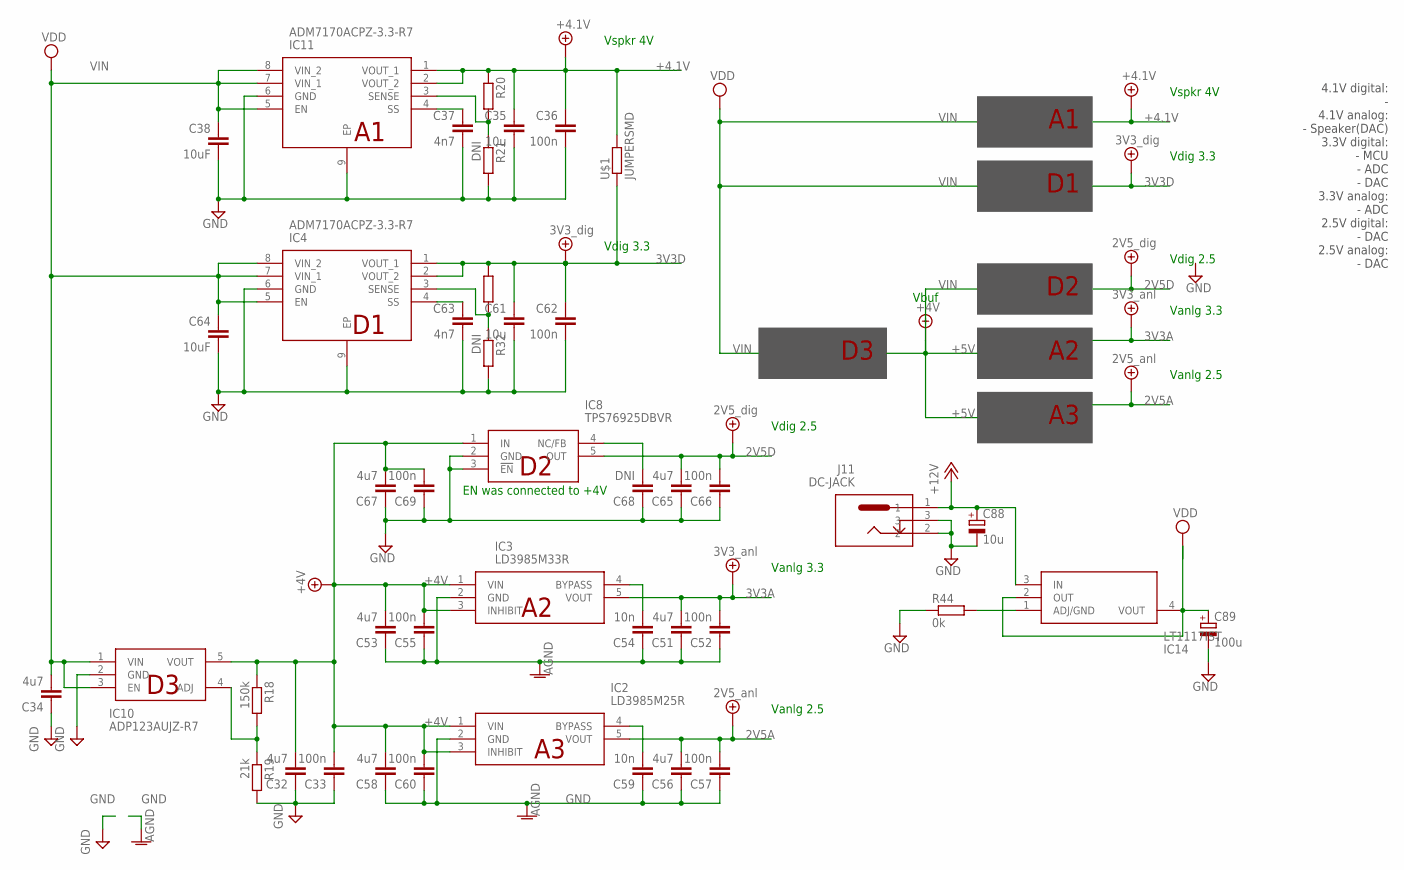
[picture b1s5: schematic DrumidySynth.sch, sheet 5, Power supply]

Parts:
C32, C34, C51, C53, C56, C58, C65, C67: 4u7; C0603K
C33, C52, C55, C57, C60, C66, C69: 100n; C0402
C35, C61: 10u; C0603
C36, C62: 100n; C0402K
C37, C63: 4n7; C0402K
C38, C64: 10uF; C0603
C54, C59: 10n; C0402K
C68: DNI; C0402K
C88: 10u; E2,5-6
C89: 100u; E2,5-6
IC2: LD3985M25R; SOT95P280X145-5N
IC3: LD3985M33R; SOT95P280X145-5N
IC4, IC11: ADM7170ACPZ-3.3-R7; SON50P300X300X80-9N
IC8: TPS76925DBVR; SOT95P280X145-5N
IC10: ADP123AUJZ-R7; SOT95P280X100-5N
IC14: LT1117IST; SOT230P700X180-4N
J11: DC-JACK; PRT00119
R18: 150k; R0603
R19: 21k; R0603
R20, R22, R44: 0k; R0603
R21, R32: DNI; R0603
U$1: JUMPERSMD; JUMPERWIDE

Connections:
2V5A: C56.2, C57.2, IC2.5 (VOUT); also elsewhere on the board
2V5D: C65.2, C66.2, IC8.5 (OUT); also elsewhere on the board
3V3A: C51.2, C52.2, IC3.5 (VOUT); also elsewhere on the board
3V3D: C61.1, C62.1, IC4.1 (VOUT_1), IC4.2 (VOUT_2), R22.1, U$1.P$1 (1); also elsewhere on the board
+4.1V: C35.1, C36.1, IC11.1 (VOUT_1), IC11.2 (VOUT_2), R20.1, U$1.P$2 (2); also elsewhere on the board
+4V: C32.2, C33.2, C53.2, C55.2, C58.2, C60.2, C67.2, C69.2, IC2.1 (VIN), IC2.3 (INHIBIT), IC3.1 (VIN), IC3.3 (INHIBIT), IC8.1 (IN), IC10.5 (VOUT), R18.1
+12V: C88.+, IC14.3 (IN), J11.1
GND: C32.1, C33.1, C34.1, C35.2, C36.2, C37.2, C38.2, C51.1, C52.1, C53.1, C54.1, C55.1, C56.1, C57.1, C58.1, C59.1, C60.1, C61.2, C62.2, C63.2, C64.2, C65.1, C66.1, C67.1, C68.1, C69.1, C88.-, C89.-, IC2.2 (GND), IC3.2 (GND), IC4.6 (GND), IC4.9 (EP), IC8.2 (GND), IC8.3 (!EN), IC10.2 (GND), IC11.6 (GND), IC11.9 (EP), J11.2, J11.3, R19.2, R21.2, R32.2, R44.1; also elsewhere on the board
unnamed: IC10.4 (ADJ), R18.2, R19.1
unnamed: IC11.3 (SENSE), R20.2, R21.1
unnamed: C63.1, IC4.4 (SS)
unnamed: IC4.3 (SENSE), R22.2, R32.1
unnamed: C54.2, IC3.4 (BYPASS)
unnamed: C68.2, IC8.4 (NC/FB)
unnamed: C59.2, IC2.4 (BYPASS)
unnamed: IC14.1 (ADJ/GND), R44.2
unnamed: C37.1, IC11.4 (SS)
VIN: C34.2, C38.1, C64.1, C89.+, IC4.5 (EN), IC4.7 (VIN_1), IC4.8 (VIN_2), IC10.1 (VIN), IC10.3 (EN), IC11.5 (EN), IC11.7 (VIN_1), IC11.8 (VIN_2), IC14.2 (OUT), IC14.4 (VOUT); also elsewhere on the board

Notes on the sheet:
Vspkr 4V
Vdig 3.3
Vdig 2.5
Vanlg 2.5
Vanlg 3.3
4.1V digital: - 4.1V analog: - Speaker(DAC) 3.3V digital: - MCU - ADC - DAC 3.3V analog: - ADC 2.5V digital: - DAC 2.5V analog: - DAC
Vbuf
EN was connected to +4V

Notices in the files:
parts and their libraries:
COPYRIGHT: Copyright (C) 2022 Ultra Librarian. All rights reserved.
